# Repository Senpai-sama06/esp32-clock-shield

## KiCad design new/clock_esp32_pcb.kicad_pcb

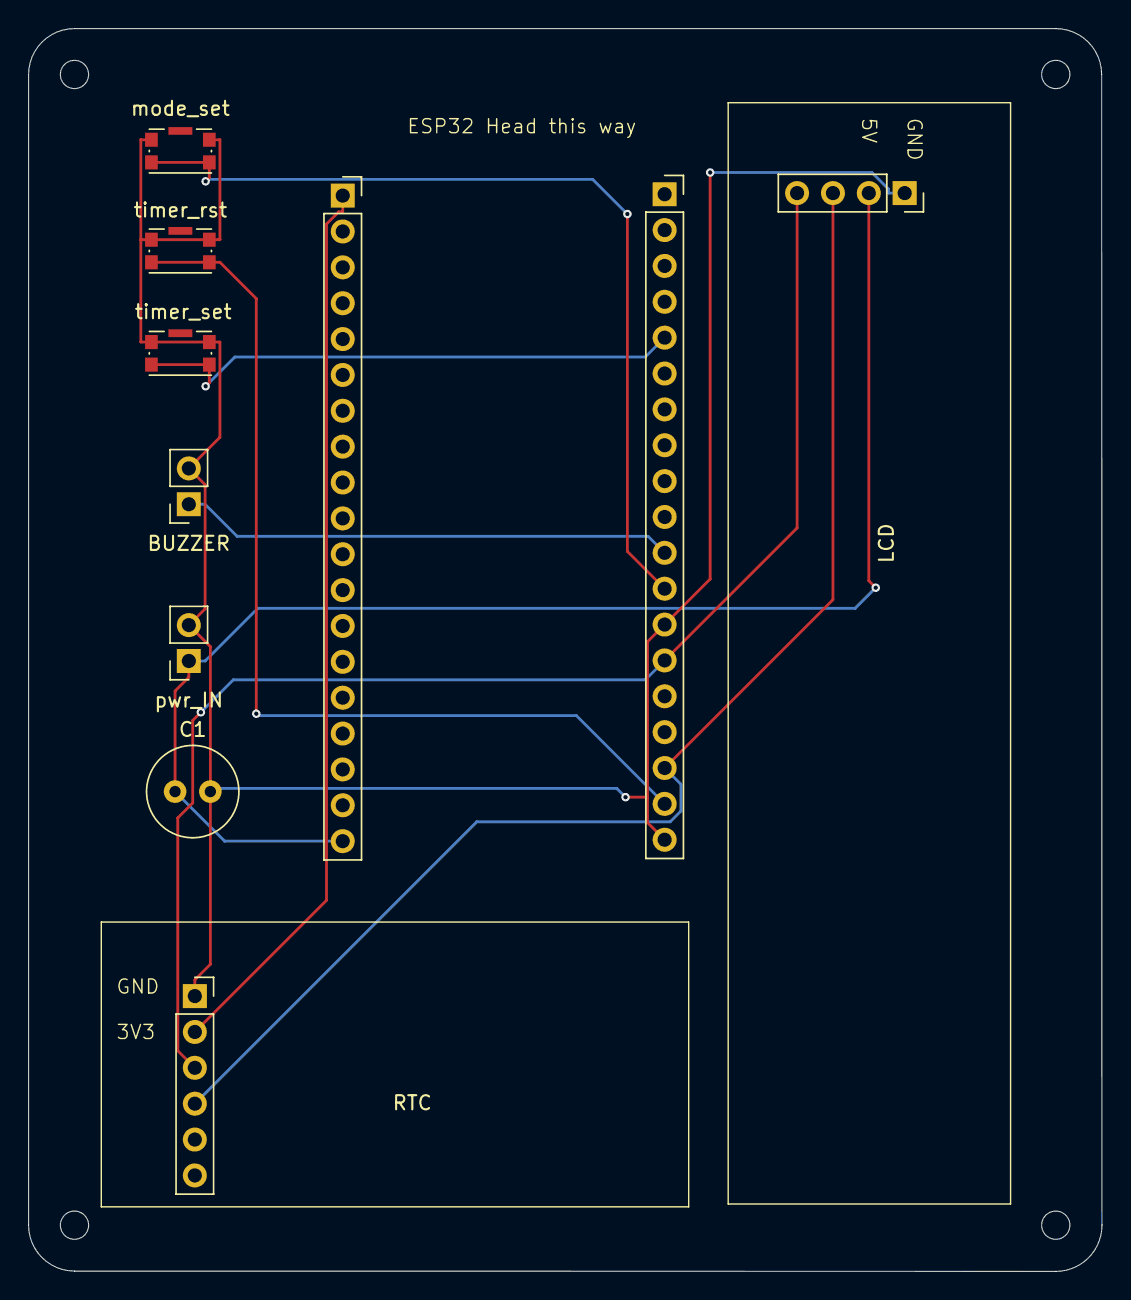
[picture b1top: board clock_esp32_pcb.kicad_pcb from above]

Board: 2 copper layers, 76.0 x 88.0 mm, 10 parts (0 on the bottom side), 9 nets.

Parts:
BUZZER: Conn_01x02_Socket; PinSocket_1x02_P2.54mm_Vertical
C1: C; C_Radial_D6.3mm_H5.0mm_P2.50mm
ESP_left1: Conn_01x19; PinSocket_1x19_P2.54mm_Vertical
ESP_right1: Conn_01x19; PinSocket_1x19_P2.54mm_Vertical
LCD: Conn_01x04_Socket; PinSocket_1x04_P2.54mm_Vertical
RTC: Conn_01x06; PinSocket_1x06_P2.54mm_Vertical
mode_set: SW_Push; SW_Push_1P1T-SH_NO_CK_KMR2xxG
pwr_IN: Conn_01x02_Socket; PinSocket_1x02_P2.54mm_Vertical
timer_rst: SW_Push; SW_Push_1P1T-SH_NO_CK_KMR2xxG
timer_set: SW_Push; SW_Push_1P1T-SH_NO_CK_KMR2xxG

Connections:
+3V3: ESP_left1.1, RTC.2
+5V: C1.1, ESP_left1.19, LCD.2, pwr_IN.1
GND: BUZZER.2, C1.2, ESP_right1.13, ESP_right1.19, LCD.1, RTC.1, mode_set.1, pwr_IN.2, timer_rst.1, timer_set.1
unnamed: BUZZER.1, ESP_right1.11
unnamed: ESP_right1.5, timer_set.2
unnamed: ESP_right1.12, mode_set.2
unnamed: ESP_right1.14, LCD.4, RTC.3
unnamed: ESP_right1.17, LCD.3, RTC.4
unnamed: ESP_right1.18, timer_rst.2

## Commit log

2025-10-08 added changes
2025-10-08 added dsn file
2025-10-08 made changes to the final layout (reduced size)
2025-10-08 check now preetham
2025-10-12 final routing completed
